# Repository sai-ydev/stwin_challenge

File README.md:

# STWIN Challenge submission - Low-Cost Sensor Hub for Anomaly Detection

This repo contains all the relevant information for our submission to the STWIN Challenge.

The Sensor Hub has the following variants: 

* Zigbee variant (Battery Powered)
  * ISM330DHCX
  * IIS2ICLX 
* Cellular variant (DC powered)
  * ISM330DHCX
  
## Applications

* Asset Tracking
* Anomaly Detection

## Project log - 12/11/2020

PCBs have arrived

## Project Log - 12/6/2020

PCBs sent to fabrication

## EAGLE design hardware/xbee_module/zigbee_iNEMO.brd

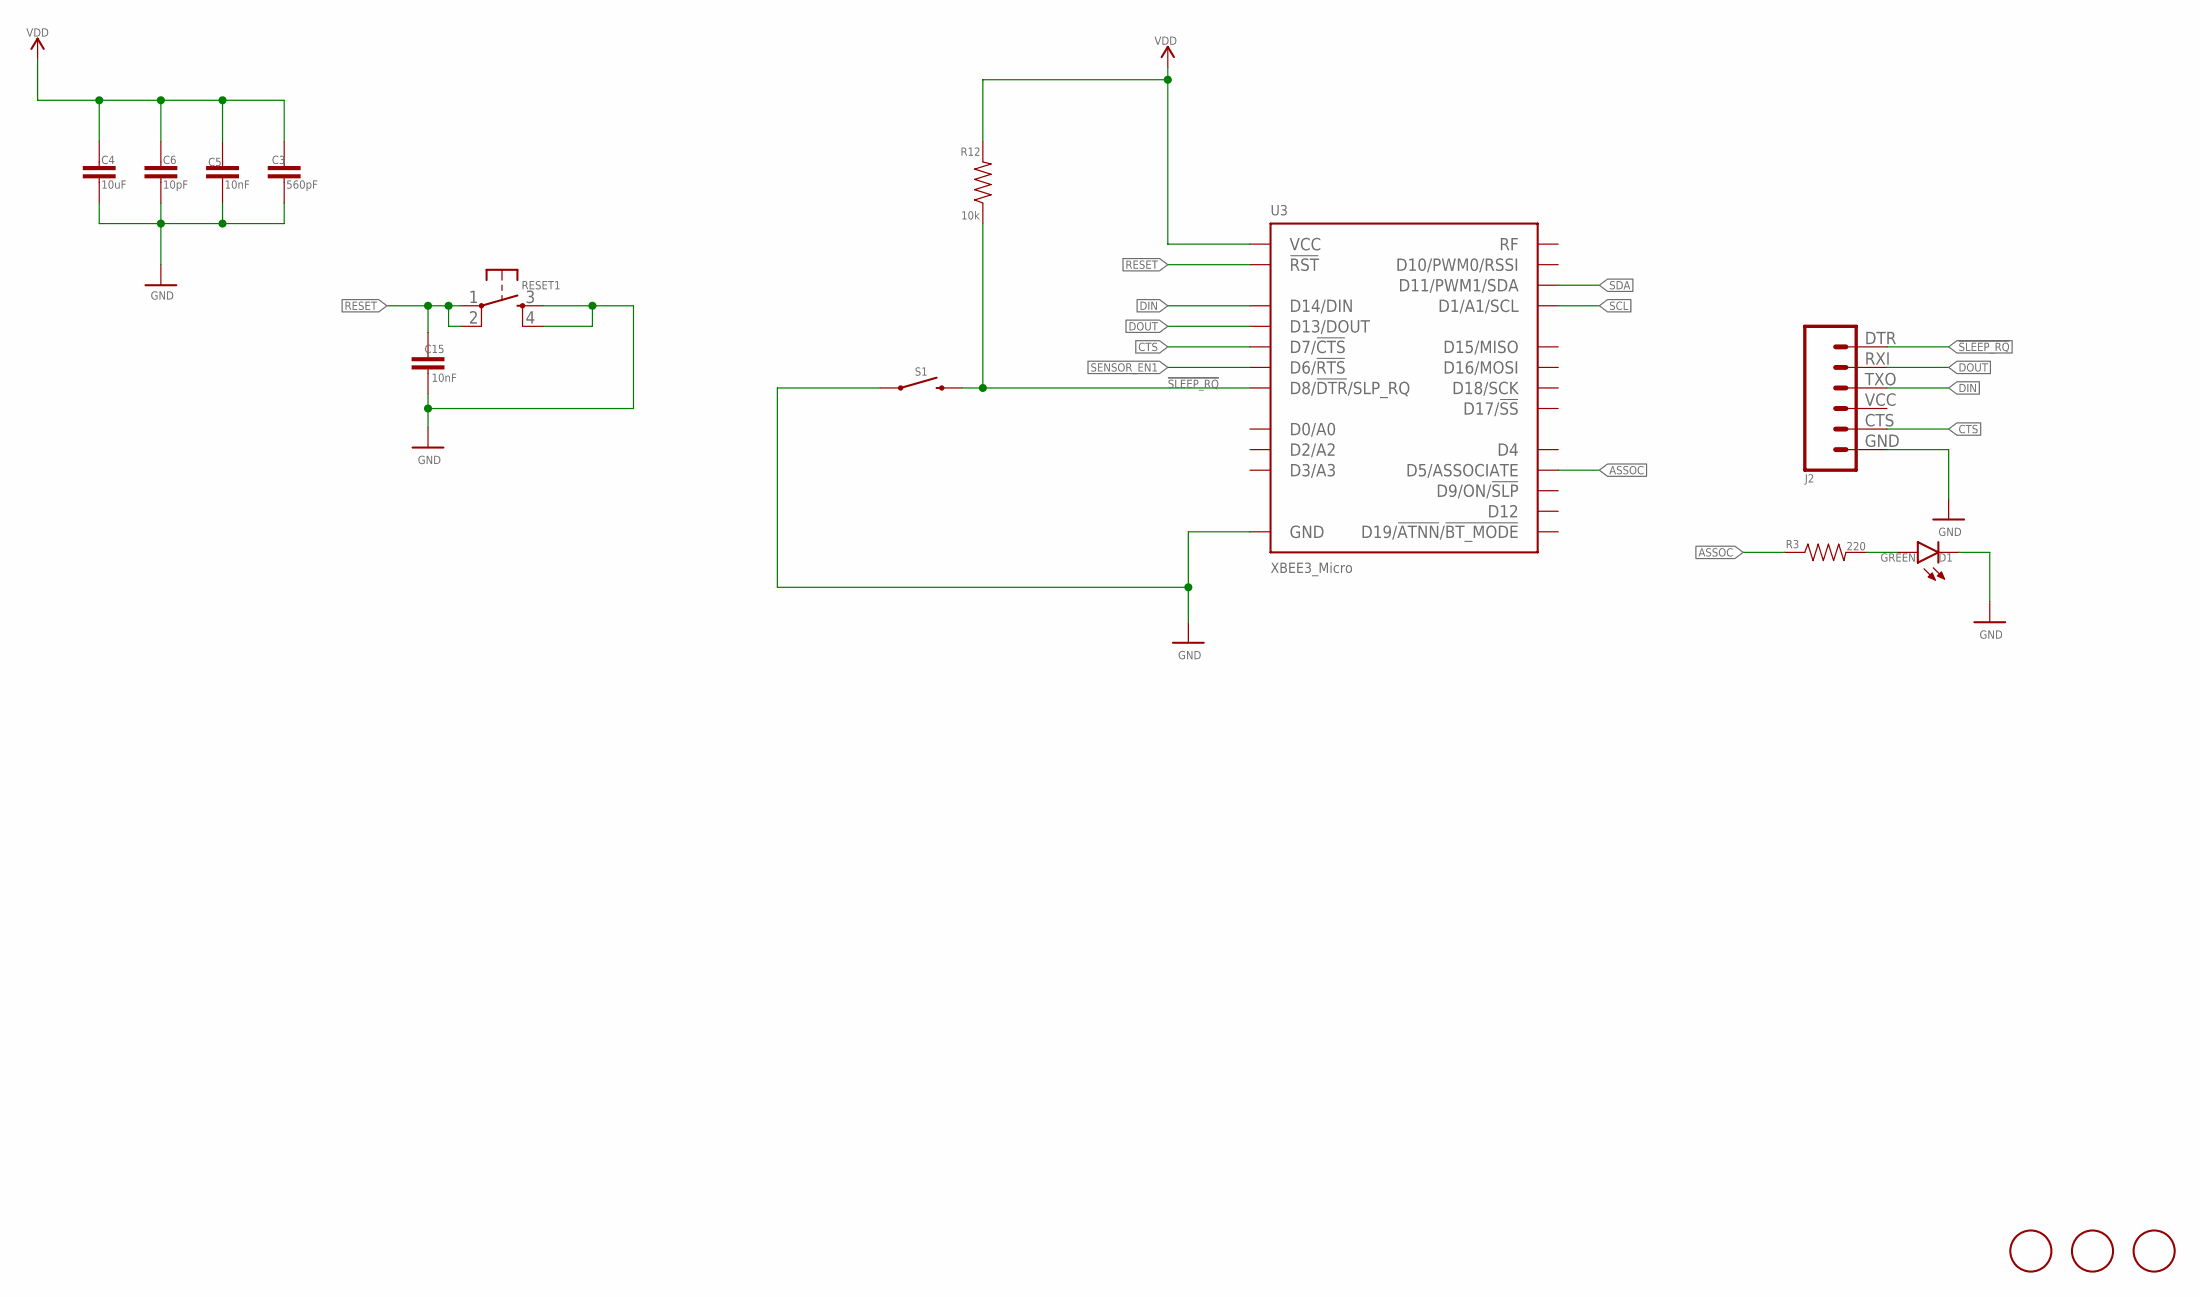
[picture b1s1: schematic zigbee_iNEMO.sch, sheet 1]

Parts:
C3: 560pF; 0603
C4: 10uF; 0603
C5, C15: 10nF; 0603
C6: 10pF; 0603
D1: GREEN; LED-0603
J2: 6_PIN_SERIAL_CABLEPTH; FTDI_BASIC
R3: 220; 0603
R12: 10k; 0603
RESET1: MOMENTARY-SWITCH-SPST-2-SMD-4.6X2.8MM; TACTILE_SWITCH_SMD_4.6X2.8MM
S1: MOMENTARY-SWITCH-SPST-SMD-4.6X2.8MM; TACTILE_SWITCH_SMD_4.6X2.8MM
U3: XBEE3_Micro; XBEE3_THING_PLUS_SPARKFUN-RF_XBEE3
U$5, U$6, U$7: FIDUCIAL; FIDUCIAL_1MM

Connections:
!SLEEP_RQ: J2.DTR (1), R12.1, S1.3 (2), S1.4 (2), U3.P$9 (D8/!DTR!/SLP_RQ)
ASSOC: R3.1, U3.P$26 (D5/ASSOCIATE)
CTS: J2.CTS (5), U3.P$24 (D7/!CTS)
DIN: J2.TXO (3), U3.P$4 (D14/DIN)
DOUT: J2.RXI (2), U3.P$3 (D13/DOUT)
GND: C3.1, C4.1, C5.1, C6.1, C15.1, D1.C, J2.GND (6), RESET1.3, RESET1.4, S1.1, S1.2 (1), U3.P$1 (GND), U3.P$10 (GND), U3.P$12 (GND), U3.P$21 (GND), U3.P$32 (GND), U3.P$34 (GND); also elsewhere on the board
unnamed: D1.A, R3.2
RESET: C15.2, RESET1.1, RESET1.2, U3.P$6 (!RST)
SCL: U3.P$30 (D1/A1/SCL); also elsewhere on the board
SDA: U3.P$8 (D11/PWM1/SDA); also elsewhere on the board
SENSOR_EN1: U3.P$27 (D6/!RTS); also elsewhere on the board
VDD: C3.2, C4.2, C5.2, C6.2, R12.2, U3.P$2 (VCC); also elsewhere on the board

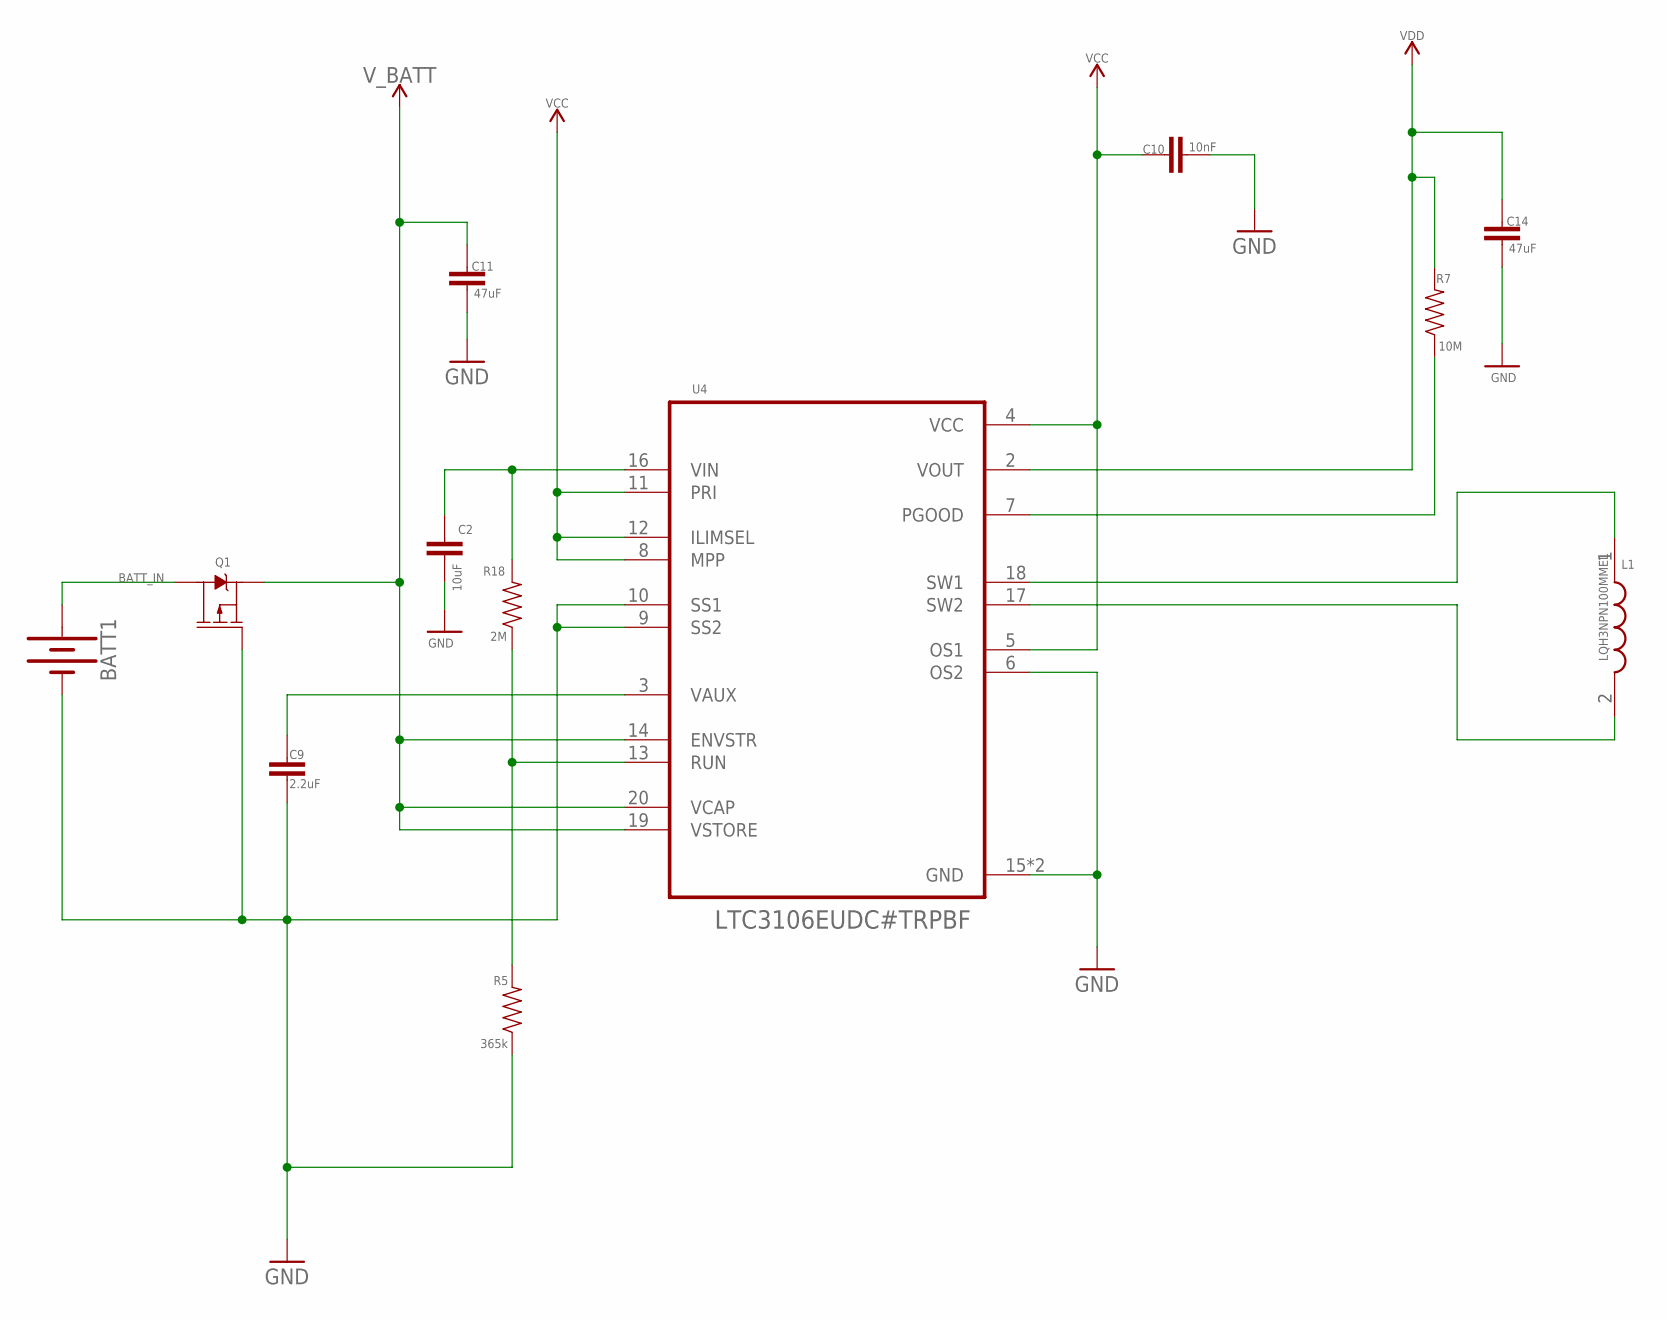
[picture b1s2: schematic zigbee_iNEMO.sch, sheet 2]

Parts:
BATT1: KEYSTONE_54KEYSTONE_2; KEYSTONE_V2
C2: 10uF; 0603
C9: 2.2uF; 0603
C10: 10nF; 0603
C11, C14: 47uF; 0603
L1: LQH3NPN100MMEL; INDPM3030X150N
Q1: 2.5A/30V/105mΩ; SOT23-3
R5: 365k; 0603
R7: 10M; 0603
R18: 2M; 0603
U4: LTC3106EUDC#TRPBF; QFN50P400X300X80-21N

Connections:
BATT_IN: BATT1.P$1 (+), BATT1.P$2 (+), BATT1.P$3 (+), Q1.3 (D)
GND: BATT1.P$4 (-), BATT1.P$5 (-), BATT1.P$6 (-), C2.2, C9.2, C10.2, C11.2, C14.2, Q1.1 (G), R5.1, U4.6 (OS2), U4.9 (SS2), U4.10 (SS1), U4.15 (GND), U4.21 (GND); also elsewhere on the board
unnamed: L1.1, U4.18 (SW1)
unnamed: L1.2, U4.17 (SW2)
unnamed: R7.1, U4.7 (PGOOD)
unnamed: C9.1, U4.3 (VAUX)
unnamed: C2.1, R18.2, U4.16 (VIN)
unnamed: R5.2, R18.1, U4.13 (RUN)
VCC: C10.1, U4.4 (VCC), U4.5 (OS1), U4.8 (MPP), U4.11 (PRI), U4.12 (ILIMSEL)
VDD: C14.1, R7.2, U4.2 (VOUT); also elsewhere on the board
V_BATT: C11.1, Q1.2 (S), U4.14 (ENVSTR), U4.19 (VSTORE), U4.20 (VCAP)

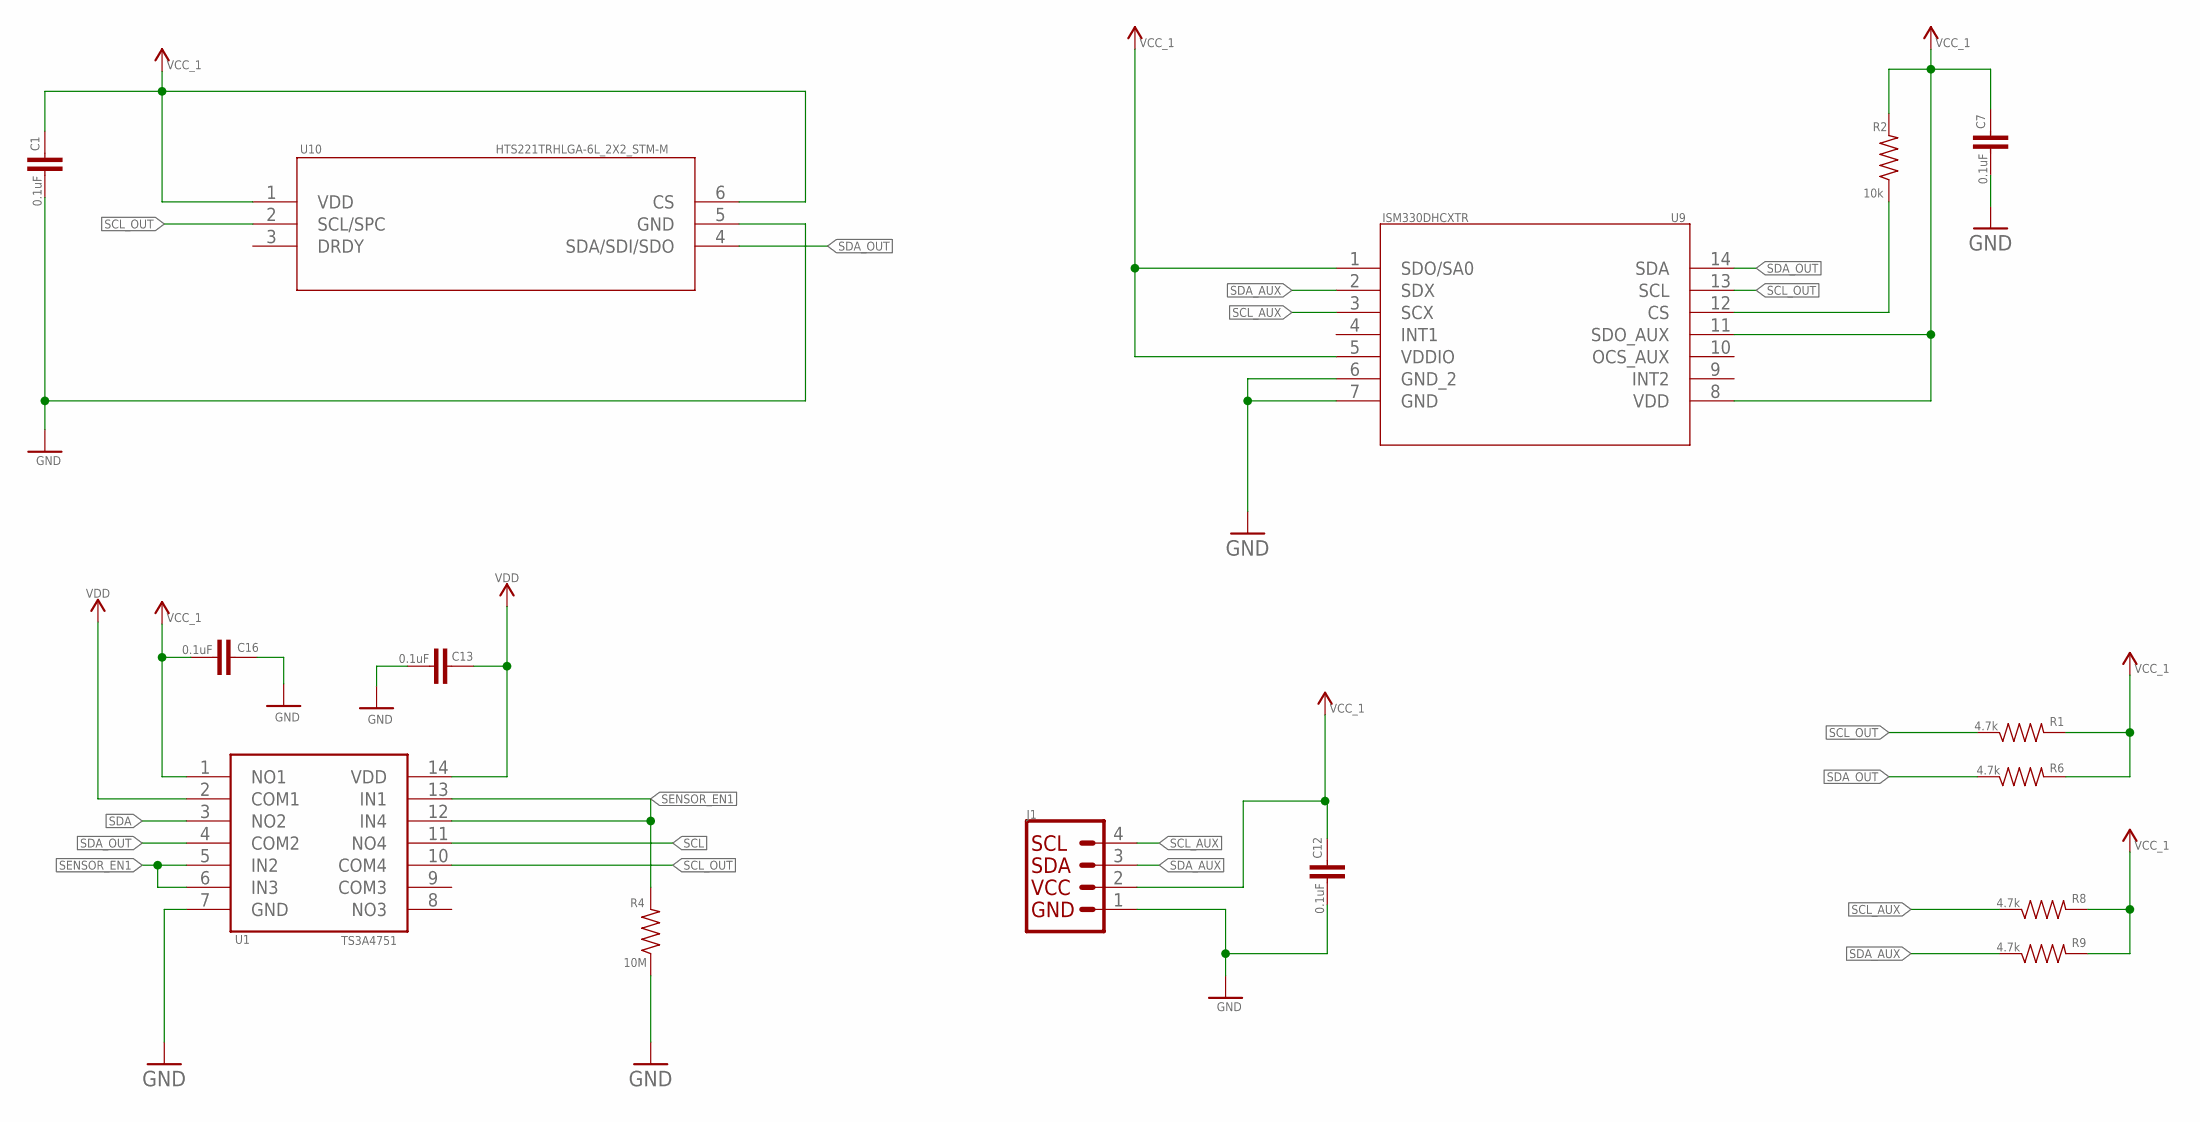
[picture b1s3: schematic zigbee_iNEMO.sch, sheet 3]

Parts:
C1, C7, C12, C13, C16: 0.1uF; 0603
J1: I2C_STANDARD; 1X04
R1, R6, R8, R9: 4.7k; 0603
R2: 10k; 0603
R4: 10M; 0603
U1: TS3A4751; 14_PIN
U9: ISM330DHCXTR; QFN_DHCXTR_STM
U10: HTS221TRHLGA-6L_2X2_STM-M; HLGA-6L_2X2_STM-M

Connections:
GND: C1.2, C7.2, C12.2, C13.2, C16.1, J1.1, R4.1, U1.7 (GND), U9.6 (GND_2), U9.7 (GND), U10.5 (GND); also elsewhere on the board
unnamed: R2.1, U9.12 (CS)
SCL: U1.11 (NO4); also elsewhere on the board
SCL_AUX: J1.4, R8.1, U9.3 (SCX)
SCL_OUT: R1.1, U1.10 (COM4), U9.13 (SCL), U10.2 (SCL/SPC)
SDA: U1.3 (NO2); also elsewhere on the board
SDA_AUX: J1.3, R9.1, U9.2 (SDX)
SDA_OUT: R6.1, U1.4 (COM2), U9.14 (SDA), U10.4 (SDA/SDI/SDO)
SENSOR_EN1: R4.2, U1.5 (IN2), U1.6 (IN3), U1.12 (IN4), U1.13 (IN1); also elsewhere on the board
VCC_1: C1.1, C7.1, C12.1, C16.2, J1.2, R1.2, R2.2, R6.2, R8.2, R9.2, U1.1 (NO1), U9.1 (SDO/SA0), U9.5 (VDDIO), U9.8 (VDD), U9.11 (SDO_AUX), U10.1 (VDD), U10.6 (CS)
VDD: C13.1, U1.2 (COM1), U1.14 (VDD); also elsewhere on the board

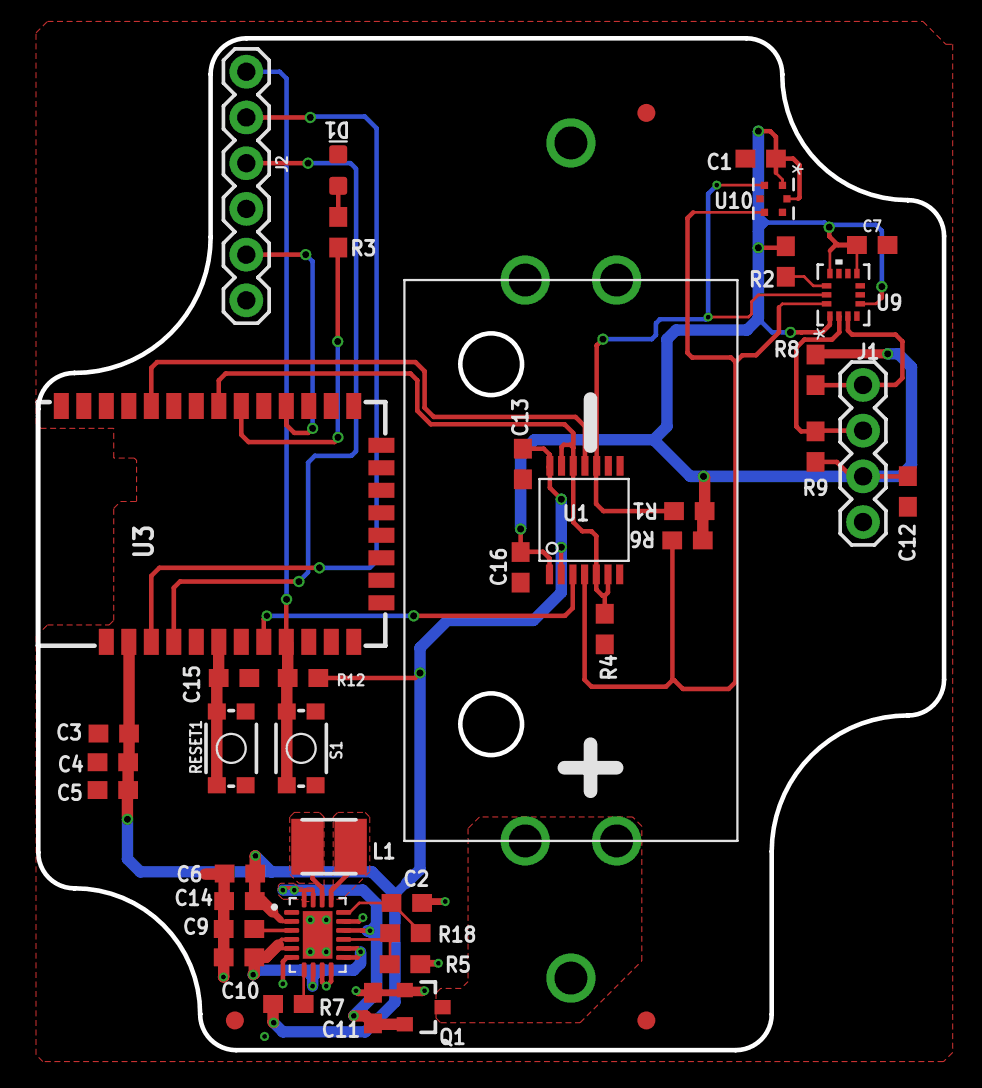
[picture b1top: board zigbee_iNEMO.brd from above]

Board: 2 copper layers, 50.3 x 56.2 mm, 42 parts (0 on the bottom side), 27 nets.

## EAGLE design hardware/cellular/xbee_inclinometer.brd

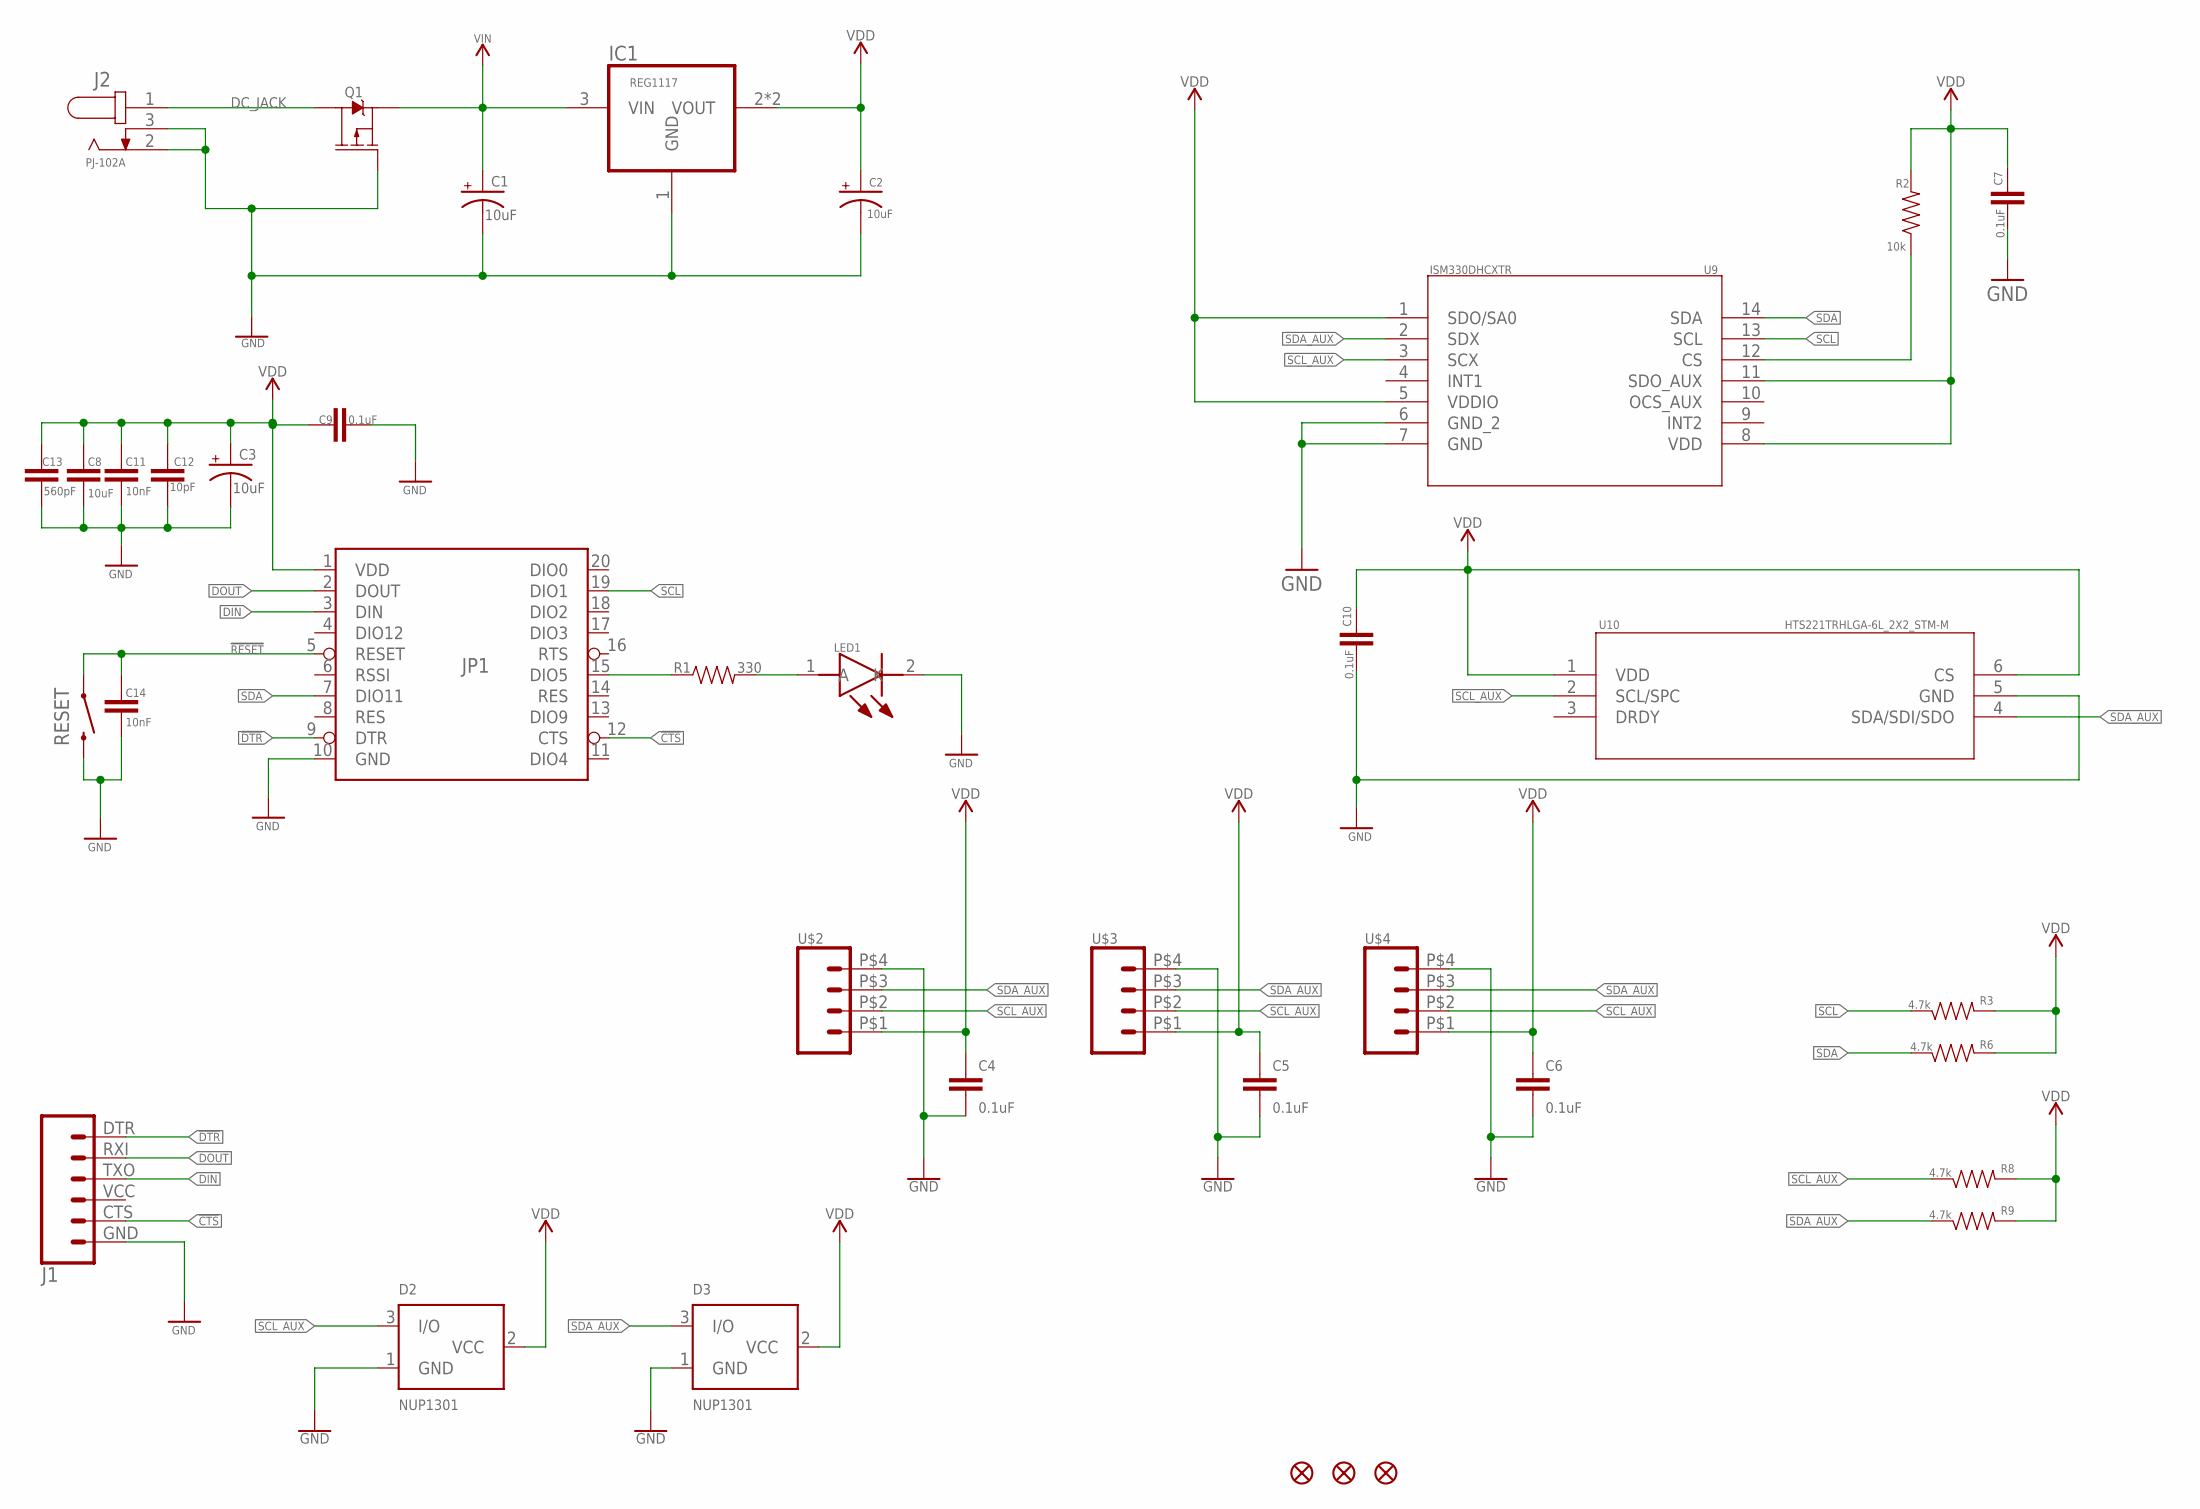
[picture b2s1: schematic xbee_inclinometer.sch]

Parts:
C1, C2, C3: 10uF; EIA3216
C4, C5, C6, C7, C9, C10: 0.1uF; 0603
C8: 10uF; 0603
C11, C14: 10nF; 0603
C12: 10pF; 0603
C13: 560pF; 0603
D2, D3: NUP1301; NUP1301_SOT-23
FID1, FID2, FID4: MICROBUILDER_FIDUCIAL""; MICROBUILDER_FIDUCIAL_1MM
IC1: REG1117; SOT223
J1: 6_PIN_SERIAL_CABLEPTH; FTDI_BASIC
J2: PJ-102A; CUI_PJ-102A
JP1: XBEESMD; XBEE-SMD
LED1: SMTL2-UWD; SMTL2UWD
Q1: 2.5A/30V/105mΩ; SOT23-3
R1: 330; 0603
R2: 10k; 0603
R3, R6, R8, R9: 4.7k; 0603
RESET: MOMENTARY-SWITCH-SPST-PTH-6.0MM; TACTILE_SWITCH_PTH_6.0MM
U9: ISM330DHCXTR; QFN_DHCXTR_STM
U10: HTS221TRHLGA-6L_2X2_STM-M; HLGA-6L_2X2_STM-M
U$2, U$3, U$4: RIGHT_ANGLED_DCFRECONN; M8_FRECONN

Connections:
!CTS: J1.CTS (5), JP1.12 (CTS)
!DTR: J1.DTR (1), JP1.9 (DTR)
!RESET: C14.1, JP1.5 (RESET), RESET.1
DC_JACK: J2.1, Q1.3 (D)
DIN: J1.TXO (3), JP1.3 (DIN)
DOUT: J1.RXI (2), JP1.2 (DOUT)
GND: C1.-, C2.-, C3.-, C4.2, C5.2, C6.2, C7.2, C8.2, C9.1, C10.2, C11.2, C12.2, C13.2, C14.2, D2.1 (GND), D3.1 (GND), IC1.1 (GND), J1.GND (6), J2.2, J2.3, JP1.10 (GND), LED1.2 (K), Q1.1 (G), RESET.3 (2), U9.6 (GND_2), U9.7 (GND), U10.5 (GND), U$2.P$4 (GND), U$3.P$4 (GND), U$4.P$4 (GND)
unnamed: JP1.15 (DIO5), R1.1
unnamed: LED1.1 (A), R1.2
unnamed: R2.1, U9.12 (CS)
SCL: JP1.19 (DIO1), R3.1, U9.13 (SCL)
SCL_AUX: D2.3 (I/O), R8.1, U9.3 (SCX), U10.2 (SCL/SPC), U$2.P$2 (SCL), U$3.P$2 (SCL), U$4.P$2 (SCL)
SDA: JP1.7 (DIO11), R6.1, U9.14 (SDA)
SDA_AUX: D3.3 (I/O), R9.1, U9.2 (SDX), U10.4 (SDA/SDI/SDO), U$2.P$3 (SDA), U$3.P$3 (SDA), U$4.P$3 (SDA)
VDD: C2.+, C3.+, C4.1, C5.1, C6.1, C7.1, C8.1, C9.2, C10.1, C11.1, C12.1, C13.1, D2.2 (VCC), D3.2 (VCC), IC1.2 (VOUT), IC1.4 (VOUT), JP1.1 (VDD), R2.2, R3.2, R6.2, R8.2, R9.2, U9.1 (SDO/SA0), U9.5 (VDDIO), U9.8 (VDD), U9.11 (SDO_AUX), U10.1 (VDD), U10.6 (CS), U$2.P$1 (VCC), U$3.P$1 (VCC), U$4.P$1 (VCC)
VIN: C1.+, IC1.3 (VIN), Q1.2 (S)

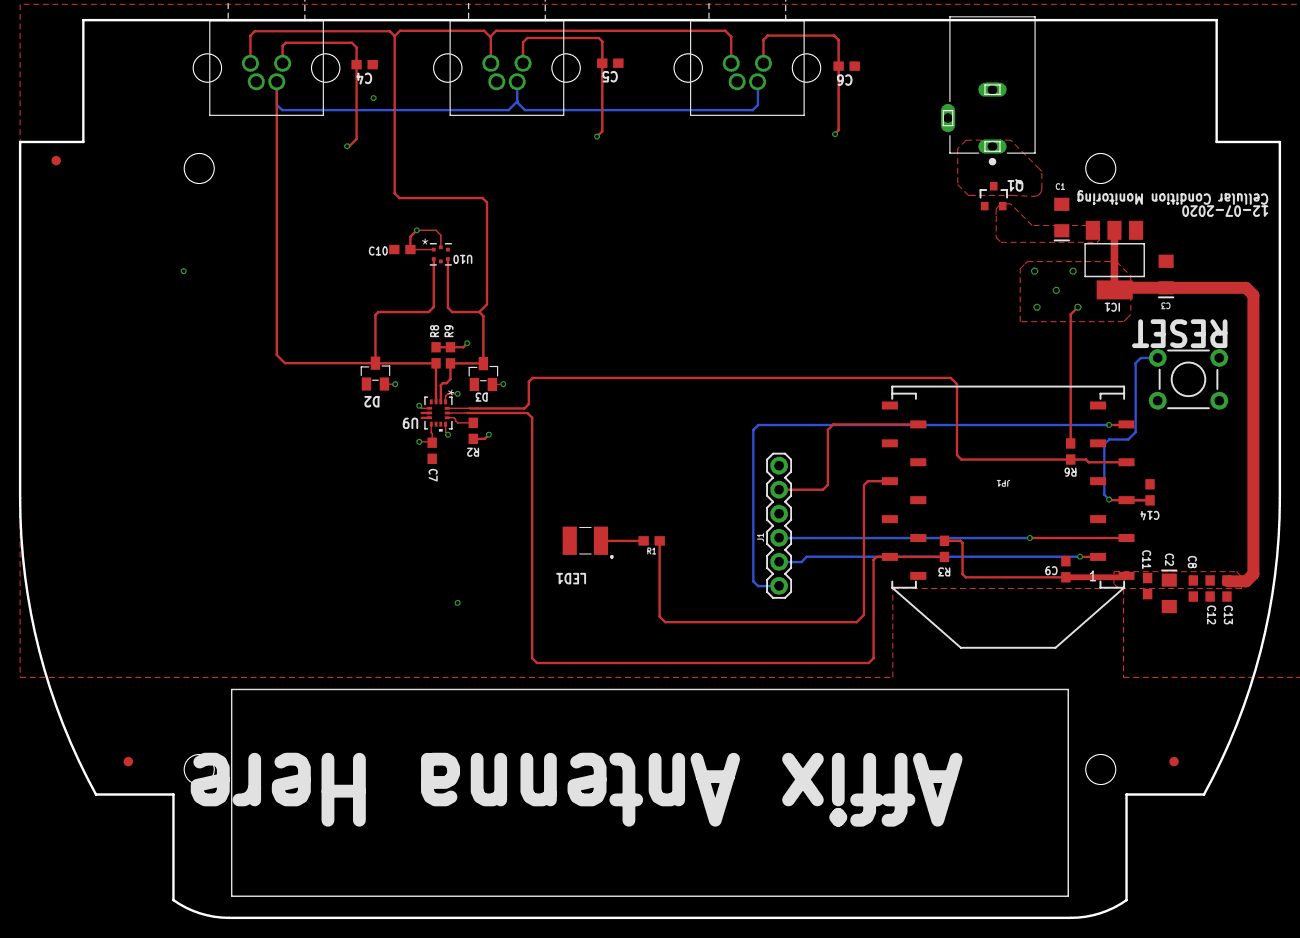
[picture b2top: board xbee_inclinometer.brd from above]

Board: 2 copper layers, 133.1 x 94.8 mm, 37 parts (0 on the bottom side), 16 nets.

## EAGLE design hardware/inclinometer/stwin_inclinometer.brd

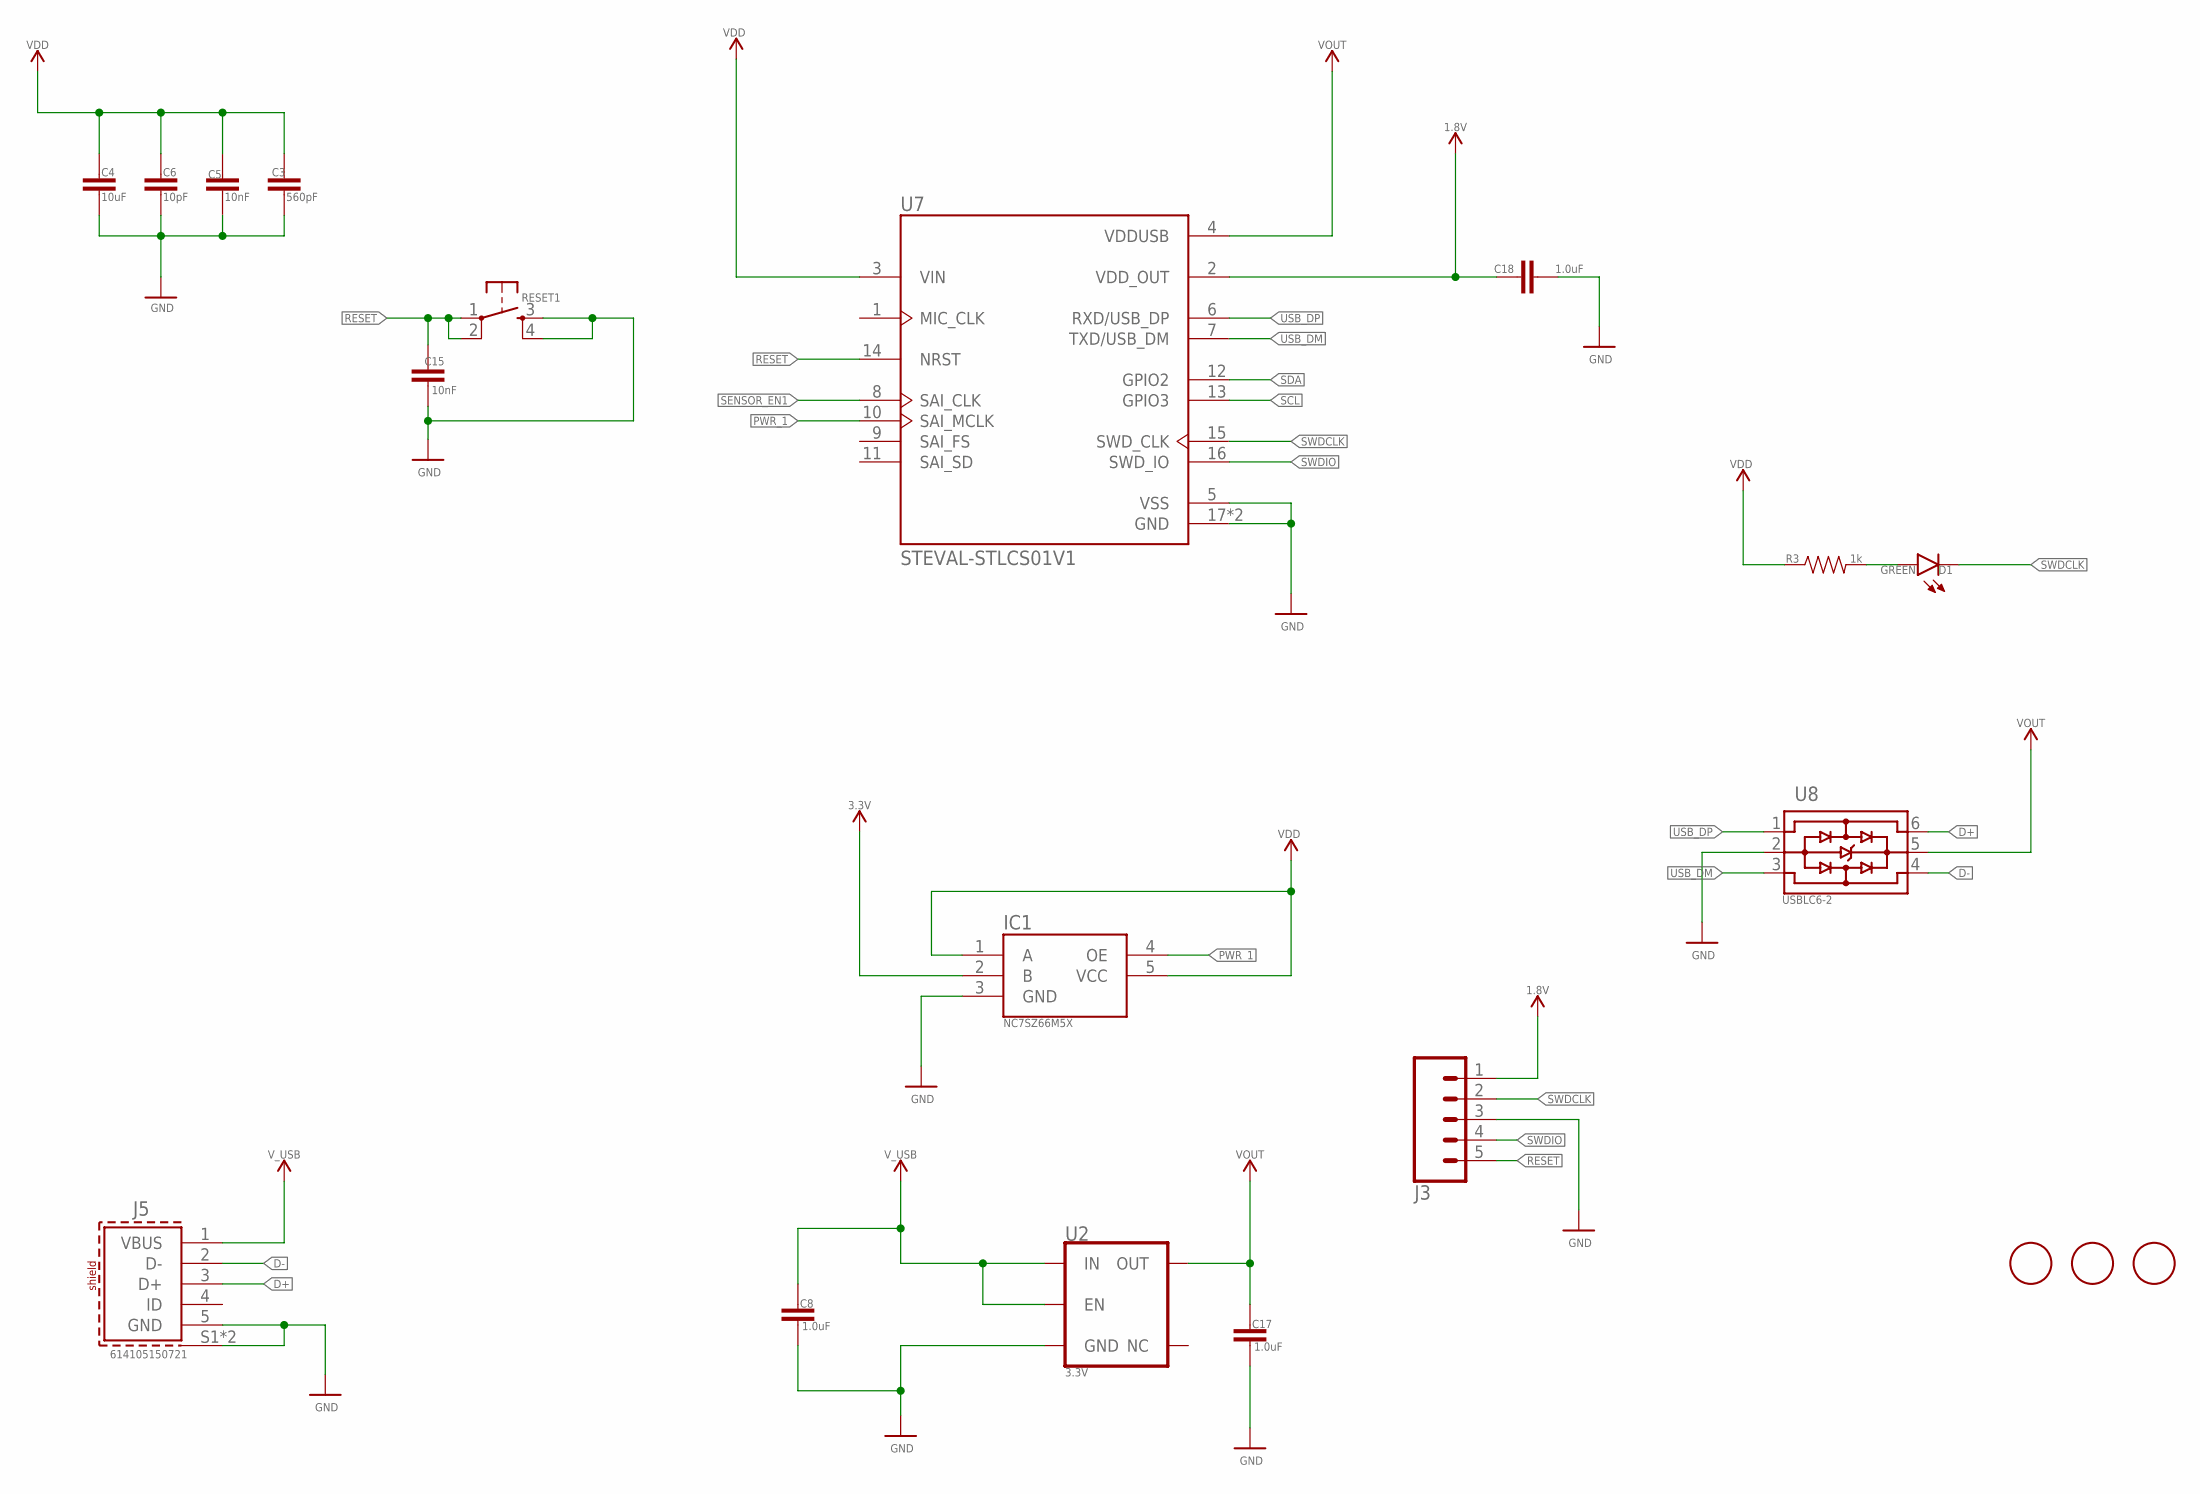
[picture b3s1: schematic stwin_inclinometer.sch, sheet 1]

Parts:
C3: 560pF; 0603
C4: 10uF; 0603
C5, C15: 10nF; 0603
C6: 10pF; 0603
C8, C17, C18: 1.0uF; 0603
D1: GREEN; LED-0603
IC1: NC7SZ66M5X; SOT95P280X145-5N
J3: CONN_05LOCK_LONGPADS; 1X05_LOCK_LONGPADS
J5: 614105150721
R3: 1k; 0603
RESET1: MOMENTARY-SWITCH-SPST-2-SMD-4.6X2.8MM; TACTILE_SWITCH_SMD_4.6X2.8MM
U2: 3.3V; SOT23-5
U7: STEVAL-STLCS01V1; XDCR_STEVAL-STLCS01V1
U8: USBLC6-2; USBLC6-2P6
U$5, U$6, U$7: FIDUCIAL; FIDUCIAL_1MM

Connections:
1.8V: C18.1, J3.1, U7.2 (VDD_OUT); also elsewhere on the board
3.3V: IC1.2 (B); also elsewhere on the board
D+: J5.3 (D+), U8.6
D-: J5.2 (D-), U8.4
GND: C3.1, C4.1, C5.1, C6.1, C8.2, C15.1, C17.2, C18.2, IC1.3 (GND), J3.3, J5.5 (GND), J5.S1 (SHIELD), J5.S2 (SHIELD), RESET1.3, RESET1.4, U2.2 (GND), U7.5 (VSS), U7.17 (GND), U7.18 (GND), U8.2; also elsewhere on the board
unnamed: D1.A, R3.2
PWR_1: IC1.4 (OE), U7.10 (SAI_MCLK)
RESET: C15.2, J3.5, RESET1.1, RESET1.2, U7.14 (NRST)
SCL: U7.13 (GPIO3); also elsewhere on the board
SDA: U7.12 (GPIO2); also elsewhere on the board
SENSOR_EN1: U7.8 (SAI_CLK); also elsewhere on the board
SWDCLK: D1.C, J3.2, U7.15 (SWD_CLK)
SWDIO: J3.4, U7.16 (SWD_IO)
USB_DM: U7.7 (TXD/USB_DM), U8.3
USB_DP: U7.6 (RXD/USB_DP), U8.1
VDD: C3.2, C4.2, C5.2, C6.2, IC1.1 (A), IC1.5 (VCC), R3.1, U7.3 (VIN); also elsewhere on the board
VOUT: C17.1, U2.5 (OUT), U7.4 (VDDUSB), U8.5
V_USB: C8.1, J5.1 (VBUS), U2.1 (IN), U2.3 (EN)

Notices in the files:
parts and their libraries:
SparkFun-Capacitors: Licensing: Creative Commons ShareAlike 4.0 International - https://creativecommons.org/licenses/by-sa/4.0
COPYRIGHT: Copyright (C) 2018 Accelerated Designs. All rights reserved
